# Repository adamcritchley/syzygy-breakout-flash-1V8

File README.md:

# SYZYGY Breakout Flash 1V8
SYZYGY Breakout Board strictly for 1.8V flash chips. I wanted a way to experiment with flash without having to spin a new board for each footprint or solder yet another BGA or TSOP. Flash programmers with ZIF adapters seemed like the best choice and SYZYGY would make it compatible with a wide range of FPGA boards. So I combined the ZIF and SYZYGY then added a clock (the SYZYGY-Breakout-FLASH-LVL even has level shifters!). This is the simpler version of the other two SYZYGY flash breakout boards but if you really wanted to use this board with other voltages then you could either change the SYZYGY DNA file to use a different VIO (which won't work on ZUBoard 1CG's dumb VIO) or use an add-on DIP board for shifting to whichever voltage your flash requires. Maybe you could take one of these [boards](https://www.amazon.com/gp/product/B0897TX932) and replace the 1.8V LDO with a 3.3V LDO? If you do and it works then let me know.

# Building Firmware
A prebuilt firmware has been provided in the 'firmware' directory. If you want to customize the SMART VIO then modify 'szg-flash-std.json' with the custom power values and use the official [SYZYGY tools](https://github.com/SYZYGYfpga/syzygy-tools/) repo to build the firmware. 

```bash
python ..\..\syzygy-tools\dna-tools\syzygy-tools.py -d ..\szg-dna\SZG-FLASH\szg-flash-std.json -f ..\..\syzygy-tools\pod-fw\avr-dna-fw-main.hex
```

# Fabrication
I use JLCPCB and OSH Park. I used the DRC rules for OSH Park so the board doesn't have any special fabrication requirements. Just pick your favorite PCB shop and color.

# FPGA Development
The board has silkscreen text with corresponding pins for Avnet's [ZUBoard 1CG](https://www.avnet.com/wps/portal/us/products/avnet-boards/avnet-board-families/zuboard-1cg/). If you use a different board then you'll have to change the silkscreen and generate new gerbers. Or you can just look up the pins for your board each time. Theoretically you can use this board with any FPGA dev board that has a SYZYGY connector then you could use the respective controller for your flash device OR find someway to expose it to AXI and PS to use it with flashrom. As I figure out specific tools that work well then I'll update this README with tutorials.

# BOM
You can find datasheets for each component in the datasheets directory. All of the components can be bought from Mouser or Digikey. 
* Epson SG5032VAN
* Texas Instrument TLV1117LV
* Aries 28-6554-11

# Future Work
I consider this board feature complete. As I find/create IP and software that works with this board then I'll update this README with tutorials on how to use them. Feel free to create a GitHub issue detailing your own success story or use case.

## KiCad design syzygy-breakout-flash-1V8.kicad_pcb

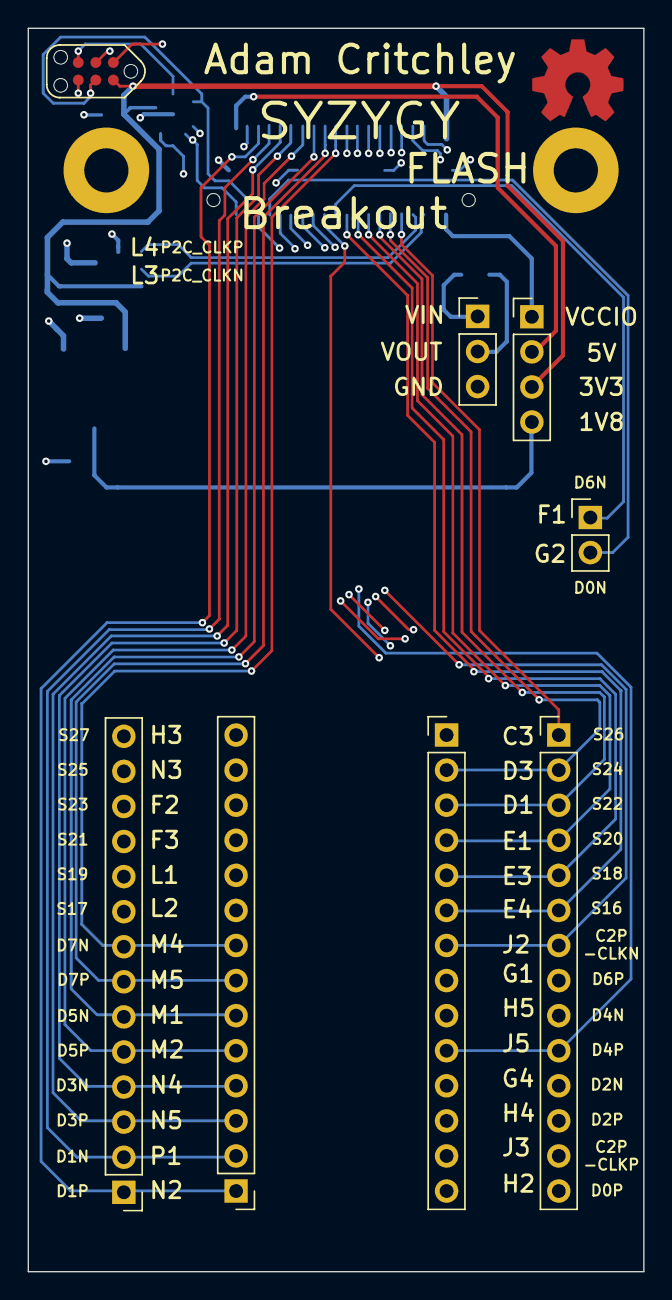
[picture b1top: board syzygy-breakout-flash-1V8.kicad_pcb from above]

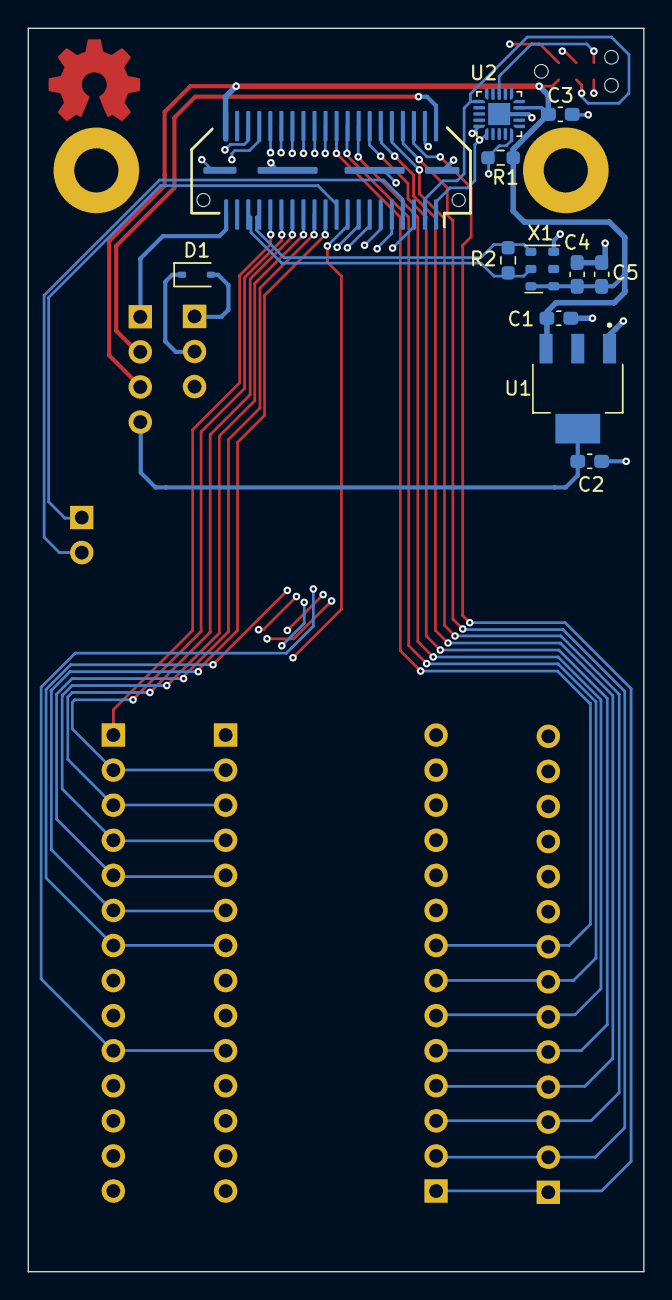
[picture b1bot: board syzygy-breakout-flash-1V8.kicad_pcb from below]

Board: 4 copper layers, 44.6 x 90.0 mm, 20 parts (12 on the bottom side), 44 nets.

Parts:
C1, C2, C4: 1uF; C_0603_1608Metric_Pad1.08x0.95mm_HandSolder
C3, C5: 0.1uF; C_0603_1608Metric_Pad1.08x0.95mm_HandSolder
D1: BAT60A; D_SOD-323
J1: SYZYGY-STD; SYZYGY-STD-POD
J2, J3, J8, J9: Conn_01x14; PinHeader_1x14_P2.54mm_Vertical
J4: Conn_01x04; PinHeader_1x04_P2.54mm_Vertical
J5: Conn_01x03; PinHeader_1x03_P2.54mm_Vertical
J6: TagConnect; TC2030-NL_SMALL
J10: Conn_01x02; PinHeader_1x02_P2.54mm_Vertical
R1: 10K; R_0603_1608Metric_Pad0.98x0.95mm_HandSolder
R2: 100R; R_0603_1608Metric_Pad0.98x0.95mm_HandSolder
U1: TLV1117LV18DCYT; SOT230P700X180-4N
U2: ATtiny44A-MMH; QFN-20-1EP_3x3mm_P0.45mm_EP1.6x1.6mm
X1: SG3225VAN; Oscillator_SMD_Silicon_Labs_LGA-6_2.5x3.2mm_P1.25mm

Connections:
+1V8: C2.1, J4.4, U1.4 (VOUT)
+3V3: C1.2, C3.1, C4.1, C5.1, J1.40 (+3.3V), J4.3, J6.2, R1.1, U1.3 (IN), U2.9 (VCC), X1.1 (OE), X1.6 (Vcc)
+5V: J1.2 (+5V), J4.2
/C2P_CLKN: J1.36 (C2P_CLKN), J2.7, J9.7
/C2P_CLKP: J1.34 (C2P_CLKP), J2.13, J9.13
/D0_N: J1.7 (S2_D0N), J10.2
/D0_P: J1.5 (S0_D0P), J2.14, J9.14
/D1_N: J1.8 (S3_D1N), J3.2, J8.2
/D1_P: J1.6 (S1_D1P), J3.1, J8.1
/D2_N: J1.11 (S6_D2N), J2.11, J9.11
/D2_P: J1.9 (S4_D2P), J2.12, J9.12
/D3_N: J1.12 (S7_D3N), J3.4, J8.4
/D3_P: J1.10 (S5_D3P), J3.3, J8.3
/D4_N: J1.15 (S10_D4N), J2.9, J9.9
/D4_P: J1.13 (S8_D4P), J2.10, J9.10
/D5_N: J1.16 (S11_D5N), J3.6, J8.6
/D5_P: J1.14 (S9_D5P), J3.5, J8.5
/D6_N: J1.19 (S14_D6N), J10.1
/D6_P: J1.17 (S12_D6P), J2.8, J9.8
/D7_N: J1.20 (S15_D7N), J3.8, J8.8
/D7_P: J1.18 (S13_D7P), J3.7, J8.7
/P2C_CLK_N: J1.35 (P2C_CLKN), R2.1, X1.5 (~OUT)
/P2C_CLK_P: J1.33 (P2C_CLKP), R2.2, X1.4 (OUT)
/Peripheral MCU/MISO: J6.1, U2.20 (PA5)
/Peripheral MCU/~RESET: J6.5, U2.13 (~RESET/PB3)
/RGA: J1.4 (R_GA), R1.2, U2.5 (AREF/PA0)
/S16: J1.21 (S16), J2.6, J9.6
/S17: J1.22 (S17), J3.9, J8.9
/S18: J1.23 (S18), J2.5, J9.5
/S19: J1.24 (S19), J3.10, J8.10
/S20: J1.25 (S20), J2.4, J9.4
/S21: J1.26 (S21), J3.11, J8.11
/S22: J1.27 (S22), J2.3, J9.3
/S23: J1.28 (S23), J3.12, J8.12
/S24: J1.29 (S24), J2.2, J9.2
/S25: J1.30 (S25), J3.13, J8.13
/S26: J1.31 (S26), J2.1, J9.1
/S27: J1.32 (S27), J3.14, J8.14
/SCL: J1.1 (SCL), J6.3, U2.1 (PA4)
/SDA: J1.3 (SDA), J6.4, U2.16 (PA6)
GND: C1.1, C2.2, C3.2, C4.2, C5.2, J1.41 (GND), J5.3, J6.6, U1.1 (GND), U2.8 (GND), U2.21 (GND), X1.3 (GND)
unnamed: D1.2 (A), J5.1
VCC: D1.1 (K), J5.2
VCCIO: J1.39 (VIO1), J4.1

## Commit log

2023-09-09 Create LICENSE
2023-09-09 Add SYZYGY DNA
2023-09-09 Fix szg dna name
2023-09-10 Updated README #2
2023-09-10 Updated README #3
